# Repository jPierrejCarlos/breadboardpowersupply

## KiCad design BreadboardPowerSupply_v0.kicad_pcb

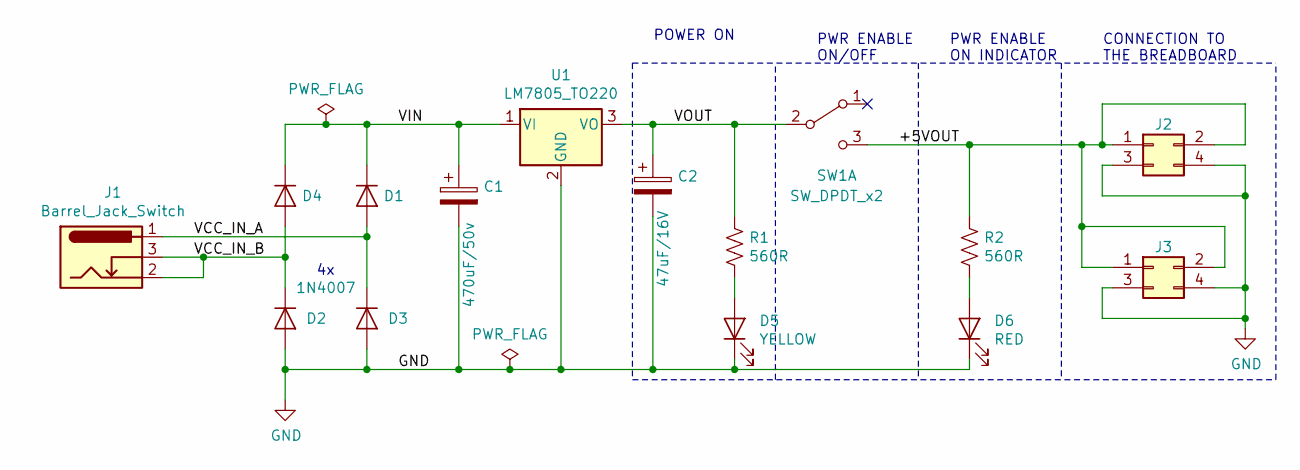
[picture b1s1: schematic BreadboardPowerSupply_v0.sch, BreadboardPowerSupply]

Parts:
C1: 470uF/50v; CP_Radial_D12.5mm_P5.00mm
C2: 47uF/16V; CP_Radial_D5.0mm_P2.00mm
D1, D2, D3, D4: 1N4007; D_DO-41_SOD81_P10.16mm_Horizontal
D5: YELLOW; LED_D3.0mm_Clear
D6: RED; LED_D3.0mm
J1: Barrel_Jack_Switch; BarrelJack_Wuerth_6941xx301002
J2, J3: Conn_02x02_Odd_Even; PinHeader_2x02_P2.54mm_Vertical
R1, R2: 560R; R_Axial_DIN0207_L6.3mm_D2.5mm_P7.62mm_Horizontal
SW1: SW_DPDT_x2; Switch_Slide_11.6x4mm_EG1218
U1: LM7805_TO220; TO-220-3_Vertical

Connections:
/+5VOUT: J2.1, J2.2, J3.1, J3.2, R2.2, SW1.3 (C)
/VCC_IN_A: D1.2 (A), D3.1 (K), J1.1
/VCC_IN_B: D2.1 (K), D4.2 (A), J1.2, J1.3
/VIN: C1.1, D1.1 (K), D4.1 (K), U1.1 (VI)
/VOUT: C2.1, R1.2, SW1.2 (B), U1.3 (VO)
GND: C1.2, C2.2, D2.2 (A), D3.2 (A), D5.1 (K), D6.1 (K), J2.3, J2.4, J3.3, J3.4, U1.2 (GND)
unnamed: D5.2 (A), R1.1
unnamed: D6.2 (A), R2.1

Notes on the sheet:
CONNECTION TO THE BREADBOARD
PWR ENABLE ON INDICATOR
PWR ENABLE ON/OFF
POWER ON

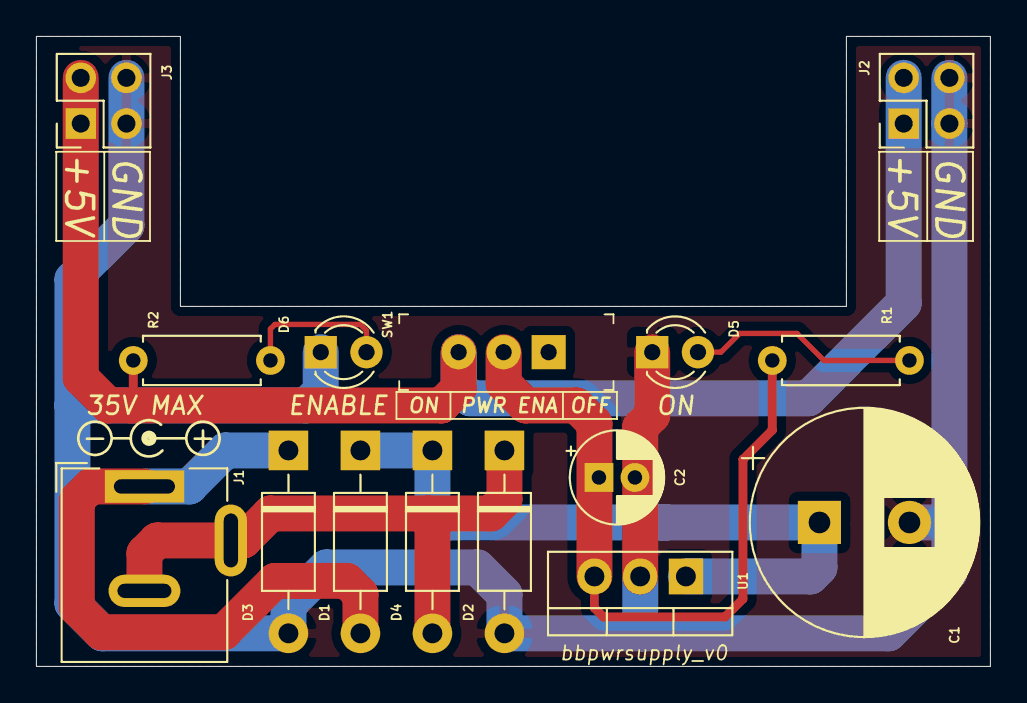
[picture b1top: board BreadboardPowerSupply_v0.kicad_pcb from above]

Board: 2 copper layers, 53.0 x 35.0 mm, 15 parts (0 on the bottom side), 8 nets.

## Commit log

2020-05-11 inicial files loaded
